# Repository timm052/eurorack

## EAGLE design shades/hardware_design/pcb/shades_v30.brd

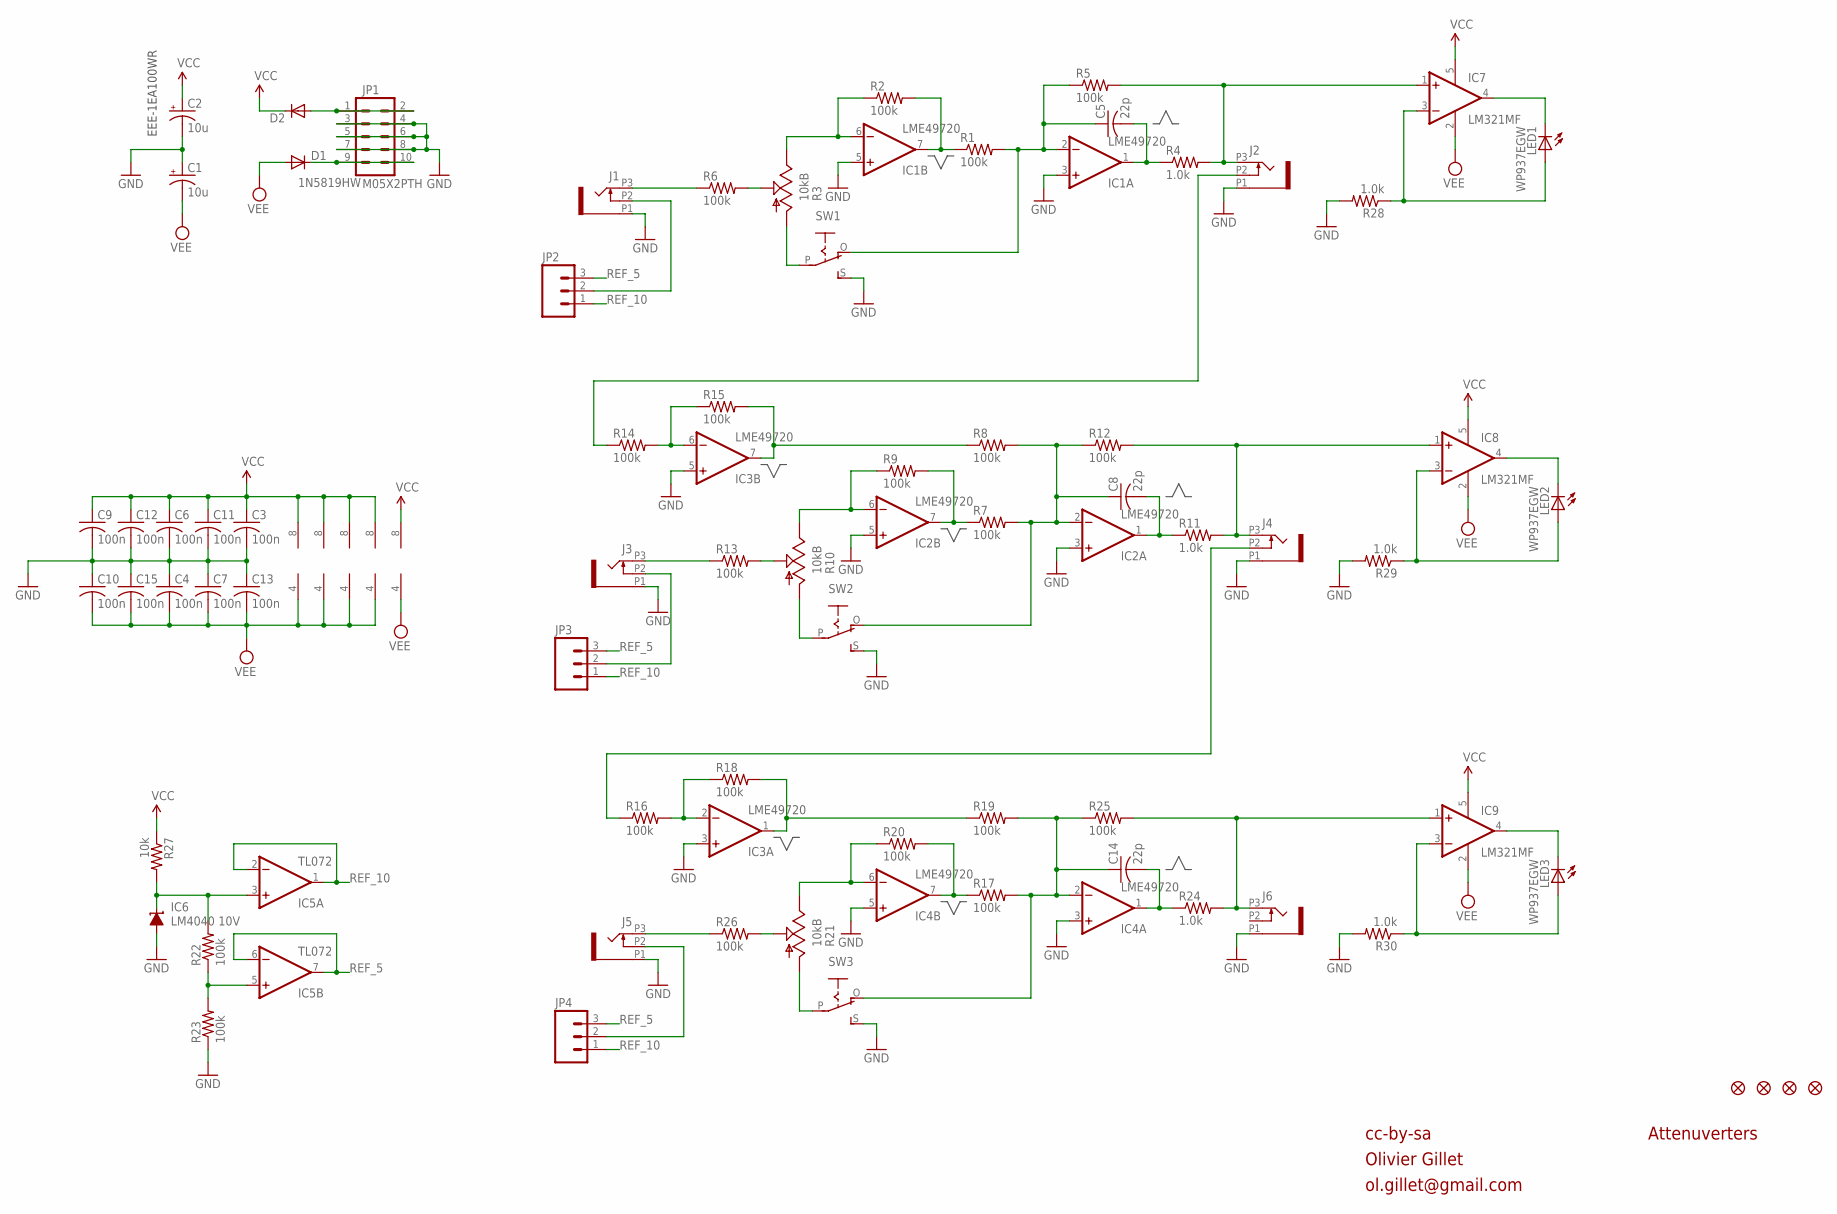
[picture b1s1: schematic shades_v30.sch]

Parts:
C1, C2: 10u; PANASONIC_B
C3, C4, C6, C7, C9, C10, C11, C12, C13, C15: 100n; C0603
C5, C8, C14: 22p; C0603
D1, D2: 1N5819HW; SOD123
F1, F2, F3, F4: FIDUCIAL1X2; FIDUCIAL-1X2
IC1, IC2, IC3, IC4: LME49720; SO08
IC5: TL072; SO08
IC6: LM4040 10V; DBZ_R-PDSO-G3
IC7, IC8, IC9: LM321MF; SOT23-5
J1, J2, J3, J4, J5, J6: PJ301_THONKICONN6; WQP_PJ_301M6
JP1: M05X2PTH; AVR_ICSP
JP2, JP3, JP4: M03PTH; 1X03
LED1, LED2, LED3: WP937EGW; LED3MM
R1, R2, R5, R6, R7, R8, R9, R12, R13, R14, R15, R16, R17, R18, R19, R20, R22, R23, R25, R26: 100k; R0603
R3, R10, R21: 10kB; ALPS_POT_VERTICAL_PS
R4, R11, R24, R28, R29, R30: 1.0k; R0603
R27: 10k; R0603
SW1, SW2, SW3: S-ON-ONSMALL_SLIDE; ES_100SP1T6B11M2QEH_SMALL

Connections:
GND: C1.+, C2.-, C3.2, C4.1, C6.2, C7.1, C9.2, C10.1, C11.2, C12.2, C13.1, C15.1, IC1.3 (+IN), IC1.5 (+IN), IC2.3 (+IN), IC2.5 (+IN), IC3.3 (+IN), IC3.5 (+IN), IC4.3 (+IN), IC4.5 (+IN), IC6.2 (A), J1.P1 (1), J2.P1 (1), J3.P1 (1), J4.P1 (1), J5.P1 (1), J6.P1 (1), JP1.3, JP1.4, JP1.5, JP1.6, JP1.7, JP1.8, R23.1, R28.2, R29.2, R30.2, SW1.S, SW2.S, SW3.S
unnamed: J1.P2 (2), JP2.2
unnamed: J3.P2 (2), JP3.2
unnamed: J5.P2 (2), JP4.2
unnamed: IC7.3 (-IN), LED1.A, R28.1
unnamed: IC5.5 (+IN), R22.1, R23.2
unnamed: D2.A, JP1.1, JP1.2
unnamed: IC7.4 (OUT), LED1.K (C)
unnamed: J1.P3 (3), R6.1
unnamed: R3.P$2 (S), R6.2
unnamed: R3.P$3 (A), SW1.P
unnamed: C5.1, IC1.2 (-IN), R1.2, R5.1, SW1.O
unnamed: IC1.6 (-IN), R2.1, R3.P$1 (E)
unnamed: IC1.7 (OUT), R1.1, R2.2
unnamed: C5.2, IC1.1 (OUT), R4.1
unnamed: J3.P3 (3), R13.1
unnamed: IC8.3 (-IN), LED2.A, R29.1
unnamed: R10.P$2 (S), R13.2
unnamed: R10.P$3 (A), SW2.P
unnamed: D1.C, JP1.9, JP1.10
unnamed: IC2.6 (-IN), R9.1, R10.P$1 (E)
unnamed: IC2.7 (OUT), R7.1, R9.2
unnamed: IC8.4 (OUT), LED2.K (C)
unnamed: C8.2, IC2.1 (OUT), R11.1
unnamed: J5.P3 (3), R26.1
unnamed: R21.P$2 (S), R26.2
unnamed: IC4.6 (-IN), R20.1, R21.P$1 (E)
unnamed: IC4.7 (OUT), R17.1, R20.2
unnamed: C14.2, IC4.1 (OUT), R24.1
unnamed: IC9.3 (-IN), LED3.A, R30.1
unnamed: IC9.4 (OUT), LED3.K (C)
unnamed: IC3.6 (-IN), R14.2, R15.1
unnamed: IC3.2 (-IN), R16.2, R18.1
unnamed: IC3.1 (OUT), R18.2, R19.1
unnamed: IC3.7 (OUT), R8.1, R15.2
unnamed: C14.1, IC4.2 (-IN), R17.2, R19.2, R25.1, SW3.O
unnamed: C8.1, IC2.2 (-IN), R7.2, R8.2, R12.1, SW2.O
OUT_1: IC7.1 (+IN), J2.P3 (3), R4.2, R5.2
OUT_2: IC8.1 (+IN), J4.P3 (3), R11.2, R12.2
OUT_3: IC9.1 (+IN), J6.P3 (3), R24.2, R25.2
REF_5: IC5.6 (-IN), IC5.7 (OUT), JP2.3, JP3.3, JP4.3
REF_10: IC5.1 (OUT), IC5.2 (-IN), JP2.1, JP3.1, JP4.1
REF_10_UNBUF: IC5.3 (+IN), IC6.1 (C), R22.2, R27.2
SEND_1: J2.P2 (2), R14.1
SEND_2: J4.P2 (2), R16.1
SW3: R21.P$3 (A), SW3.P
VCC: C2.+, C3.1, C6.1, C9.1, C11.1, C12.1, D2.C, IC1.8 (V+), IC2.8 (V+), IC3.8 (V+), IC4.8 (V+), IC5.8 (V+), IC7.5 (V+), IC8.5 (V+), IC9.5 (V+), R27.1
VEE: C1.-, C4.2, C7.2, C10.2, C13.2, C15.2, D1.A, IC1.4 (V-), IC2.4 (V-), IC3.4 (V-), IC4.4 (V-), IC5.4 (V-), IC7.2 (V-), IC8.2 (V-), IC9.2 (V-)

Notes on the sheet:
cc-by-sa
Olivier Gillet
ol.gillet@gmail.com
Attenuverters
EEE-1EA100WR

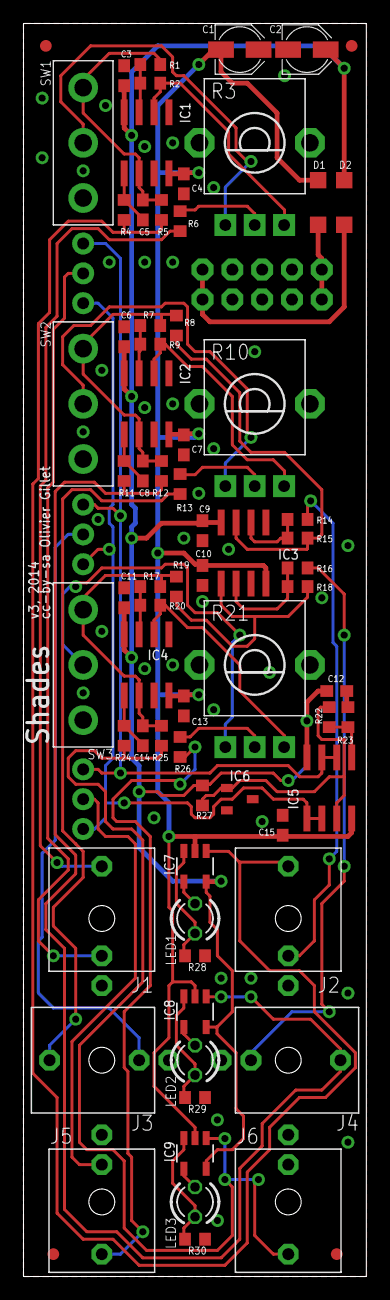
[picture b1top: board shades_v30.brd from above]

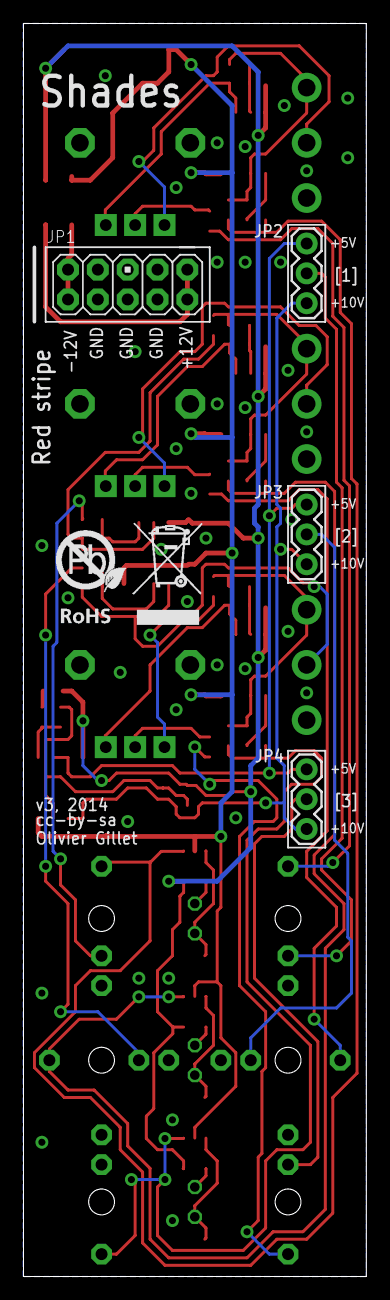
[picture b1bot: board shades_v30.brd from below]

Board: 2 copper layers, 29.2 x 106.7 mm, 77 parts (5 on the bottom side), 48 nets.

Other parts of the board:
U$2: ROHS

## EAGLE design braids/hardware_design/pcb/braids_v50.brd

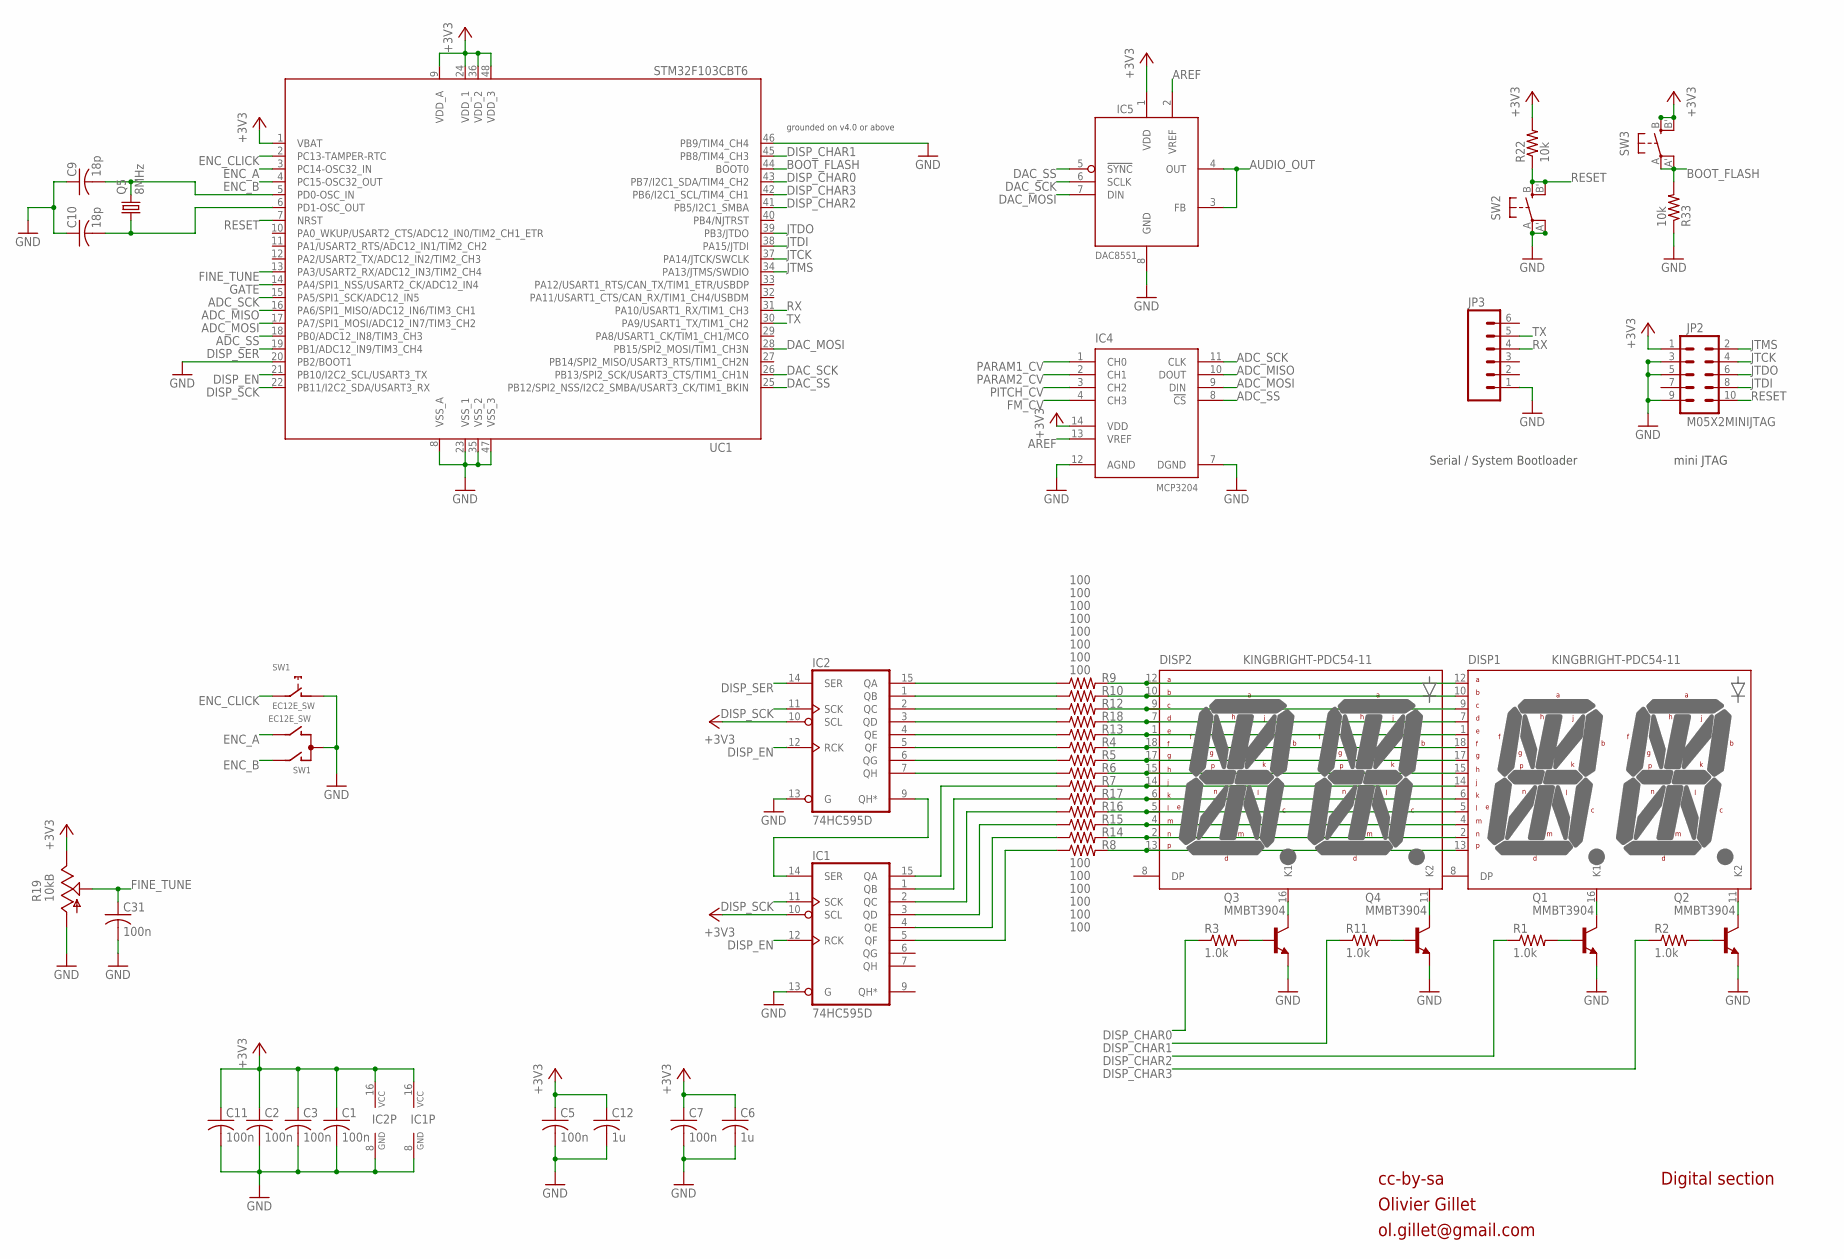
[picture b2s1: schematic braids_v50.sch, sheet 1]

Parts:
C1, C2, C3, C5, C7, C11, C31: 100n; C0603
C6, C12: 1u; C0603
C9, C10: 18p; C0603
DISP1, DISP2: KINGBRIGHT-PDC54-11; PDC54
IC1, IC2: 74HC595D; SO16
IC4: MCP3204; SO14
IC5: DAC8551; MSOP-8
JP2: M05X2MINIJTAG; 2X5-1.27
JP3: M06SIP; 1X06
Q1, Q2, Q3, Q4: MMBT3904; SOT23-BEC
Q5: 8MHz; HC49UP
R1, R2, R3, R11: 1.0k; R0603
R4, R5, R6, R7, R8, R9, R10, R12, R13, R14, R15, R16, R17, R18: 100; R0603
R19: 10kB; ALPS_POT_VERTICAL_PS
R22, R33: 10k; R0603
SW1: EC12E_SW; ALPS_EC12E_SW
SW2, SW3: EVQQ2; EVQ-Q2
UC1: STM32F103CBT6; LQFP48

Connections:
+3V3: C1.1, C2.1, C3.1, C5.1, C6.1, C7.1, C11.1, C12.1, IC1.10 (SCL), IC1.16 (VCC), IC2.10 (SCL), IC2.16 (VCC), IC4.14 (VDD), IC5.1 (VDD), JP2.1, R19.P$1 (E), R22.2, SW3.B (S), SW3.B' (S1), UC1.1 (VBAT), UC1.9 (VDD_A), UC1.24 (VDD_1), UC1.36 (VDD_2), UC1.48 (VDD_3); also elsewhere on the board
ADC_MISO: IC4.10 (DOUT), UC1.16 (PA6/SPI1_MISO/ADC12_IN6/TIM3_CH1)
ADC_MOSI: IC4.9 (DIN), UC1.17 (PA7/SPI1_MOSI/ADC12_IN7/TIM3_CH2)
ADC_SCK: IC4.11 (CLK), UC1.15 (PA5/SPI1_SCK/ADC12_IN5)
ADC_SS: IC4.8 (!CS), UC1.18 (PB0/ADC12_IN8/TIM3_CH3)
AREF: IC4.13 (VREF), IC5.2 (VREF); also elsewhere on the board
AUDIO_OUT: IC5.3 (FB), IC5.4 (OUT); also elsewhere on the board
BOOT_FLASH: R33.2, SW3.A, SW3.A' (P1), UC1.44 (BOOT0)
DAC_MOSI: IC5.7 (DIN), UC1.28 (PB15/SPI2_MOSI/TIM1_CH3N)
DAC_SCK: IC5.6 (SCLK), UC1.26 (PB13/SPI2_SCK/USART3_CTS/TIM1_CH1N)
DAC_SS: IC5.5 (!SYNC), UC1.25 (PB12/SPI2_NSS/I2C2_SMBA/USART3_CK/TIM1_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)
DISP_CHAR0: R3.1, UC1.43 (PB7/I2C1_SDA/TIM4_CH2)
DISP_CHAR1: R11.1, UC1.45 (PB8/TIM4_CH3)
DISP_CHAR2: R1.1, UC1.41 (PB5/I2C1_SMBA)
DISP_CHAR3: R2.1, UC1.42 (PB6/I2C1_SCL/TIM4_CH1)
DISP_EN: IC1.12 (RCK), IC2.12 (RCK), UC1.21 (PB10/I2C2_SCL/USART3_TX)
DISP_SCK: IC1.11 (SCK), IC2.11 (SCK), UC1.22 (PB11/I2C2_SDA/USART3_RX)
DISP_SER: IC2.14 (SER), UC1.19 (PB1/ADC12_IN9/TIM3_CH4)
ENC_A: SW1.B, UC1.3 (PC14-OSC32_IN)
ENC_B: SW1.A, UC1.4 (PC15-OSC32_OUT)
ENC_CLICK: SW1.E (2), UC1.2 (PC13-TAMPER-RTC)
FINE_TUNE: C31.1, R19.P$2 (S), UC1.13 (PA3/USART2_RX/ADC12_IN3/TIM2_CH4)
FM_CV: IC4.4 (CH3); also elsewhere on the board
GATE: UC1.14 (PA4/SPI1_NSS/USART2_CK/ADC12_IN4); also elsewhere on the board
GND: C1.2, C2.2, C3.2, C5.2, C6.2, C7.2, C9.1, C10.1, C11.2, C12.2, C31.2, IC1.8 (GND), IC1.13 (G), IC2.8 (GND), IC2.13 (G), IC4.7 (DGND), IC4.12 (AGND), IC5.8 (GND), JP2.3, JP2.5, JP2.9, JP3.1, Q1.E, Q2.E, Q3.E, Q4.E, R19.P$3 (A), R33.1, SW1.C, SW1.D (1), SW2.A, SW2.A' (P1), UC1.8 (VSS_A), UC1.20 (PB2/BOOT1), UC1.23 (VSS_1), UC1.35 (VSS_2), UC1.46 (PB9/TIM4_CH4), UC1.47 (VSS_3); also elsewhere on the board
JTCK: JP2.4, UC1.37 (PA14/JTCK/SWCLK)
JTDI: JP2.8, UC1.38 (PA15/JTDI)
JTDO: JP2.6, UC1.39 (PB3/JTDO)
JTMS: JP2.2, UC1.34 (PA13/JTMS/SWDIO)
unnamed: DISP2.16 (K1), Q3.C
unnamed: DISP2.11 (K2), Q4.C
unnamed: DISP1.16 (K1), Q1.C
unnamed: DISP1.11 (K2), Q2.C
unnamed: Q3.B, R3.2
unnamed: Q4.B, R11.2
unnamed: C9.2, Q5.2, UC1.5 (PD0-OSC_IN)
unnamed: C10.2, Q5.1, UC1.6 (PD1-OSC_OUT)
unnamed: Q1.B, R1.2
unnamed: Q2.B, R2.2
unnamed: DISP1.12 (A), DISP2.12 (A), R9.2
unnamed: DISP1.10 (B), DISP2.10 (B), R10.2
unnamed: DISP1.9 (C), DISP2.9 (C), R12.2
unnamed: DISP1.7 (D), DISP2.7 (D), R18.2
unnamed: DISP1.1 (E), DISP2.1 (E), R13.2
unnamed: DISP1.18 (F), DISP2.18 (F), R4.2
unnamed: DISP1.17 (G), DISP2.17 (G), R5.2
unnamed: DISP1.15 (H), DISP2.15 (H), R6.2
unnamed: DISP1.14 (J), DISP2.14 (J), R7.2
unnamed: DISP1.6 (K), DISP2.6 (K), R17.2
unnamed: DISP1.5 (L), DISP2.5 (L), R16.2
unnamed: DISP1.4 (M), DISP2.4 (M), R15.2
unnamed: DISP1.2 (N), DISP2.2 (N), R14.2
unnamed: DISP1.13, DISP2.13, R8.2
unnamed: IC2.7 (QH), R6.1
unnamed: IC1.14 (SER), IC2.9 (QH*)
unnamed: IC2.15 (QA), R9.1
unnamed: IC2.1 (QB), R10.1
unnamed: IC2.2 (QC), R12.1
unnamed: IC2.3 (QD), R18.1
unnamed: IC2.4 (QE), R13.1
unnamed: IC2.5 (QF), R4.1
unnamed: IC2.6 (QG), R5.1
unnamed: IC1.15 (QA), R7.1
unnamed: IC1.1 (QB), R17.1
unnamed: IC1.2 (QC), R16.1
unnamed: IC1.3 (QD), R15.1
unnamed: IC1.4 (QE), R14.1
unnamed: IC1.5 (QF), R8.1
PARAM1_CV: IC4.1 (CH0); also elsewhere on the board
PARAM2_CV: IC4.2 (CH1); also elsewhere on the board
PITCH_CV: IC4.3 (CH2); also elsewhere on the board
RESET: JP2.10, R22.1, SW2.B (S), SW2.B' (S1), UC1.7 (NRST)
RX: JP3.4, UC1.31 (PA10/USART1_RX/TIM1_CH3)
TX: JP3.5, UC1.30 (PA9/USART1_TX/TIM1_CH2)

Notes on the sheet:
cc-by-sa
Olivier Gillet
ol.gillet@gmail.com
Serial / System Bootloader
mini JTAG
Digital section
grounded on v4.0 or above

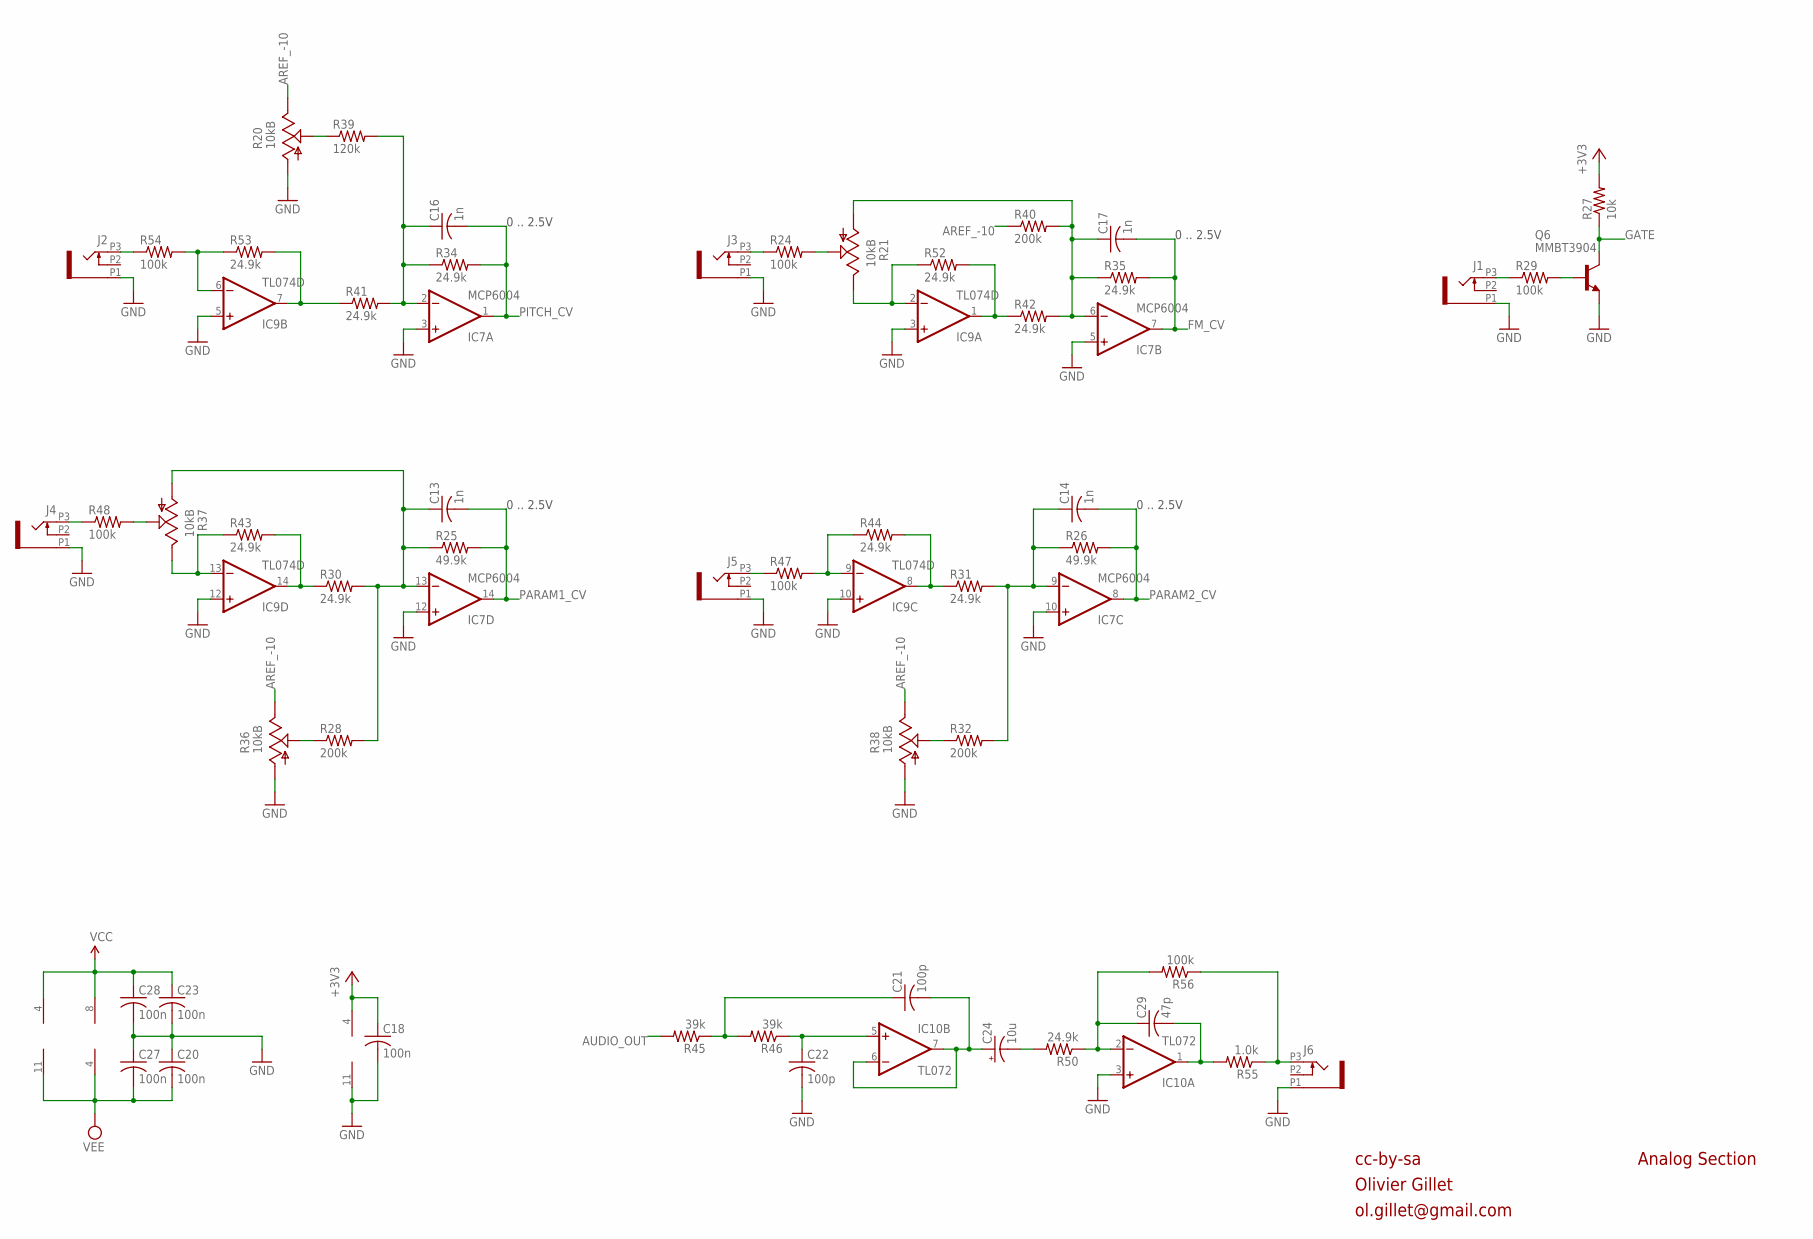
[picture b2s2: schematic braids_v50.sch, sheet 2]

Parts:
C13, C14, C16, C17: 1n; C0603
C18, C20, C23, C27, C28: 100n; C0603
C21, C22: 100p; C0603
C24: 10u; PANASONIC_B
C29: 47p; C0603
IC7: MCP6004; SO14
IC9: TL074D; SO14
IC10: TL072; SO08
J1, J2, J3, J4, J5, J6: PJ301_THONKICONN6; WQP_PJ_301M6
Q6: MMBT3904; SOT23-BEC
R20, R21, R36, R37, R38: 10kB; ALPS_POT_VERTICAL_PS
R24, R29, R47, R48, R54, R56: 100k; R0603
R25, R26: 49.9k; R0603
R27: 10k; R0603
R28, R32, R40: 200k; R0603
R30, R31, R34, R35, R41, R42, R43, R44, R50, R52, R53: 24.9k; R0603
R39: 120k; R0603
R45, R46: 39k; R0603
R55: 1.0k; R0603

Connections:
+3V3: C18.1, IC7.4 (V+), R27.2; also elsewhere on the board
AREF_-10: R20.P$1 (E), R36.P$1 (E), R38.P$1 (E), R40.1; also elsewhere on the board
AUDIO_OUT: R45.2; also elsewhere on the board
FM_CV: C17.2, IC7.7 (OUT), R35.2; also elsewhere on the board
GATE: Q6.C, R27.1; also elsewhere on the board
GND: C18.2, C20.1, C22.2, C23.2, C27.1, C28.2, IC7.3 (+IN), IC7.5 (+IN), IC7.10 (+IN), IC7.11 (V-), IC7.12 (+IN), IC9.3 (+IN), IC9.5 (+IN), IC9.10 (+IN), IC9.12 (+IN), IC10.3 (+IN), J1.P1 (1), J2.P1 (1), J3.P1 (1), J4.P1 (1), J5.P1 (1), J6.P1 (1), Q6.E, R20.P$3 (A), R36.P$3 (A), R38.P$3 (A); also elsewhere on the board
unnamed: IC9.7 (OUT), R41.1, R53.2
unnamed: R20.P$2 (S), R39.1
unnamed: J2.P3 (3), R54.1
unnamed: C16.1, IC7.2 (-IN), R34.1, R39.2, R41.2
unnamed: IC9.6 (-IN), R53.1, R54.2
unnamed: J3.P3 (3), R24.1
unnamed: J4.P3 (3), R48.1
unnamed: R21.P$2 (S), R24.2
unnamed: IC9.13 (-IN), R37.P$1 (E), R43.1
unnamed: IC9.14 (OUT), R30.1, R43.2
unnamed: IC9.2 (-IN), R21.P$1 (E), R52.1
unnamed: IC9.1 (OUT), R42.1, R52.2
unnamed: C17.1, IC7.6 (-IN), R21.P$3 (A), R35.1, R40.2, R42.2
unnamed: J1.P3 (3), R29.1
unnamed: IC9.8 (OUT), R31.1, R44.2
unnamed: C13.1, IC7.13 (-IN), R25.1, R28.2, R30.2, R37.P$3 (A)
unnamed: J5.P3 (3), R47.1
unnamed: R28.1, R36.P$2 (S)
unnamed: R37.P$2 (S), R48.2
unnamed: IC9.9 (-IN), R44.1, R47.2
unnamed: R32.1, R38.P$2 (S)
unnamed: Q6.B, R29.2
unnamed: C21.2, C24.+, IC10.6 (-IN), IC10.7 (OUT)
unnamed: C24.-, R50.2
unnamed: C22.1, IC10.5 (+IN), R46.1
unnamed: C14.1, IC7.9 (-IN), R26.1, R31.2, R32.2
unnamed: C21.1, R45.1, R46.2
unnamed: J6.P3 (3), R55.1, R56.1
unnamed: C29.2, IC10.1 (OUT), R55.2
unnamed: C29.1, IC10.2 (-IN), R50.1, R56.2
PARAM1_CV: C13.2, IC7.14 (OUT), R25.2; also elsewhere on the board
PARAM2_CV: C14.2, IC7.8 (OUT), R26.2; also elsewhere on the board
PITCH_CV: C16.2, IC7.1 (OUT), R34.2; also elsewhere on the board
VCC: C23.1, C28.1, IC9.4 (V+), IC10.8 (V+); also elsewhere on the board
VEE: C20.2, C27.2, IC9.11 (V-), IC10.4 (V-); also elsewhere on the board

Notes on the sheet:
cc-by-sa
Olivier Gillet
ol.gillet@gmail.com
Analog Section
0 .. 2.5V

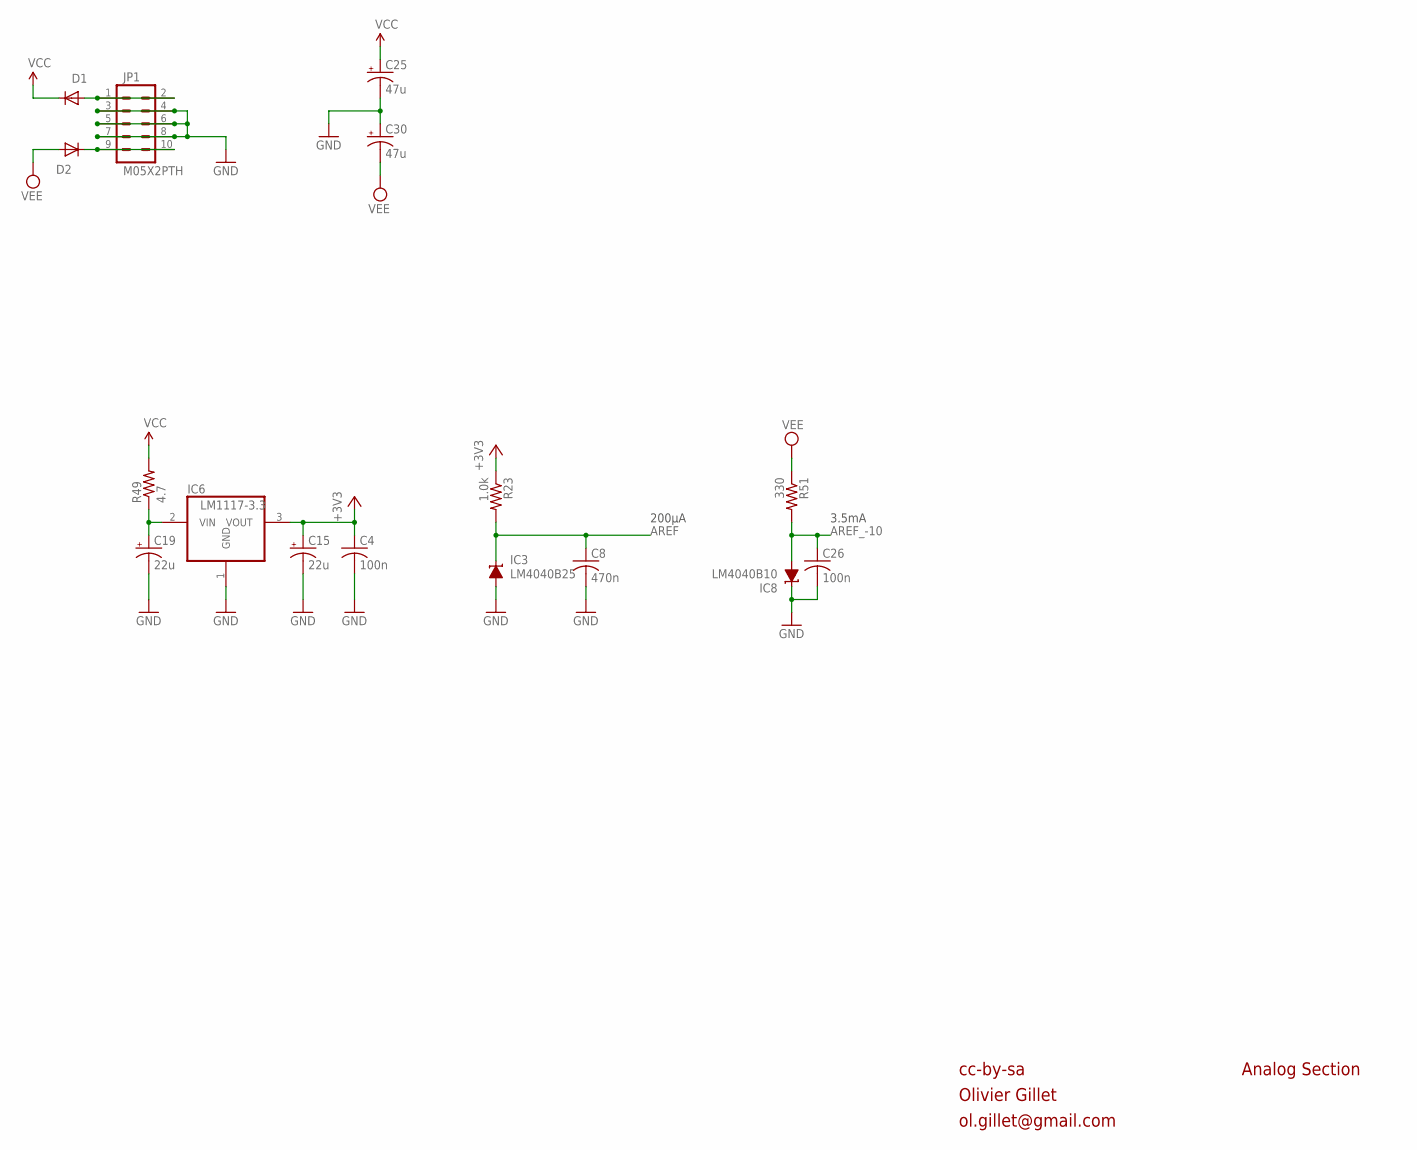
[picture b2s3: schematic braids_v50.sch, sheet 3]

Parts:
C4, C26: 100n; C0603
C8: 470n; C0603
C15, C19: 22u; PANASONIC_C
C25, C30: 47u; PANASONIC_D
D1, D2: 1N5819HW; SOD123
IC3: LM4040B25; DBZ_R-PDSO-G3
IC6: LM1117-3.3; TO252
IC8: LM4040B10; DBZ_R-PDSO-G3
JP1: M05X2PTH; AVR_ICSP
R23: 1.0k; R0603
R49: 4.7; R1206
R51: 330; R0603

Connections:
+3V3: C4.1, C15.+, IC6.3 (VOUT), R23.1; also elsewhere on the board
AREF: C8.1, IC3.1 (C), R23.2; also elsewhere on the board
AREF_-10: C26.1, IC8.2 (A), R51.2; also elsewhere on the board
GND: C4.2, C8.2, C15.-, C19.-, C25.-, C26.2, C30.+, IC3.2 (A), IC6.1 (GND), IC8.1 (C), JP1.3, JP1.4, JP1.5, JP1.6, JP1.7, JP1.8; also elsewhere on the board
unnamed: C19.+, IC6.2 (VIN), R49.1
unnamed: D1.A, JP1.1, JP1.2
unnamed: D2.C, JP1.9, JP1.10
VCC: C25.+, D1.C, R49.2; also elsewhere on the board
VEE: C30.-, D2.A, R51.1; also elsewhere on the board

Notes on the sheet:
3.5mA
200µA
cc-by-sa
Olivier Gillet
ol.gillet@gmail.com
Analog Section

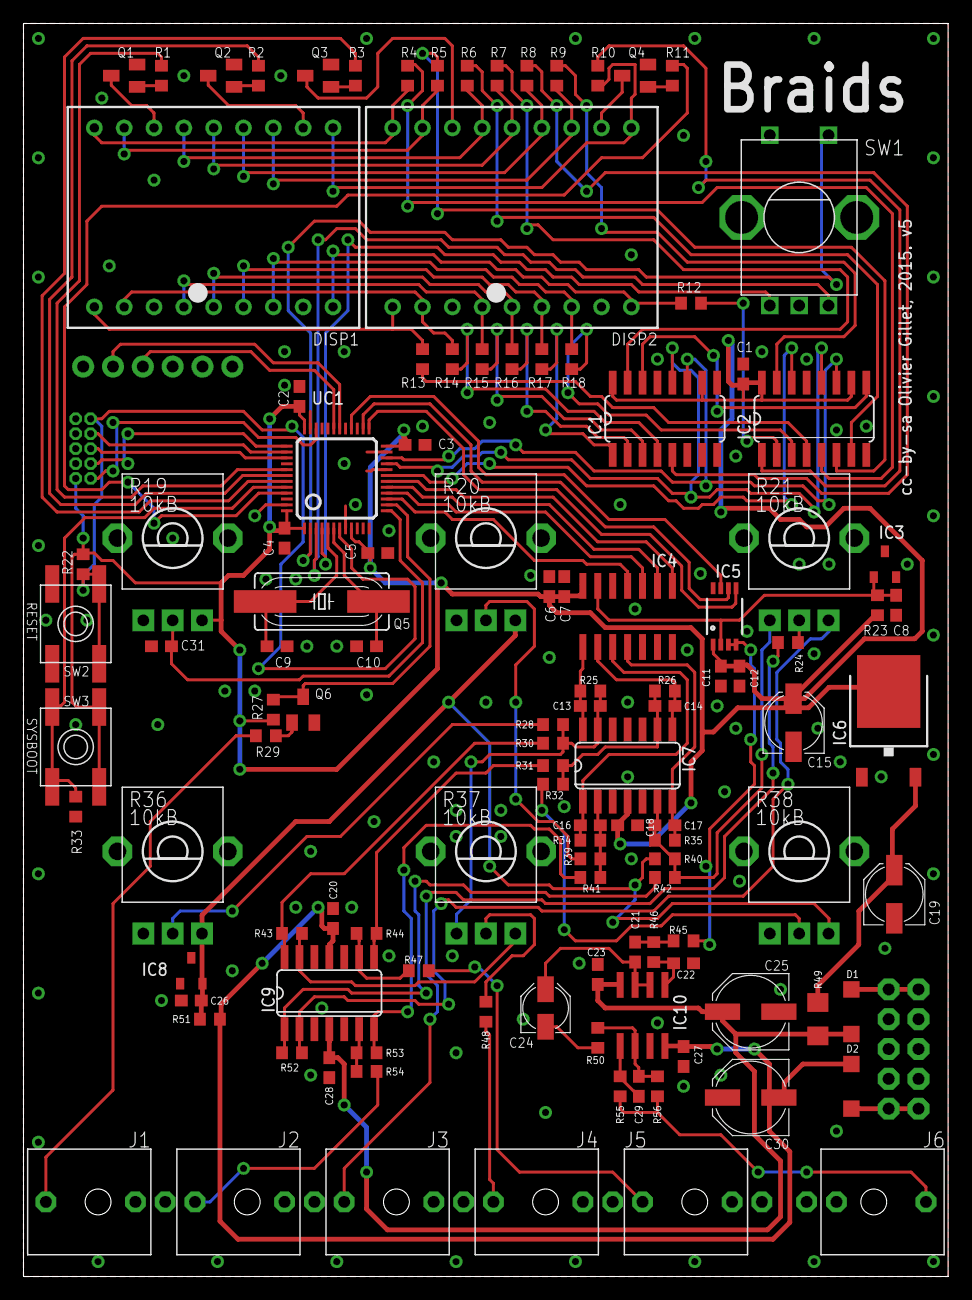
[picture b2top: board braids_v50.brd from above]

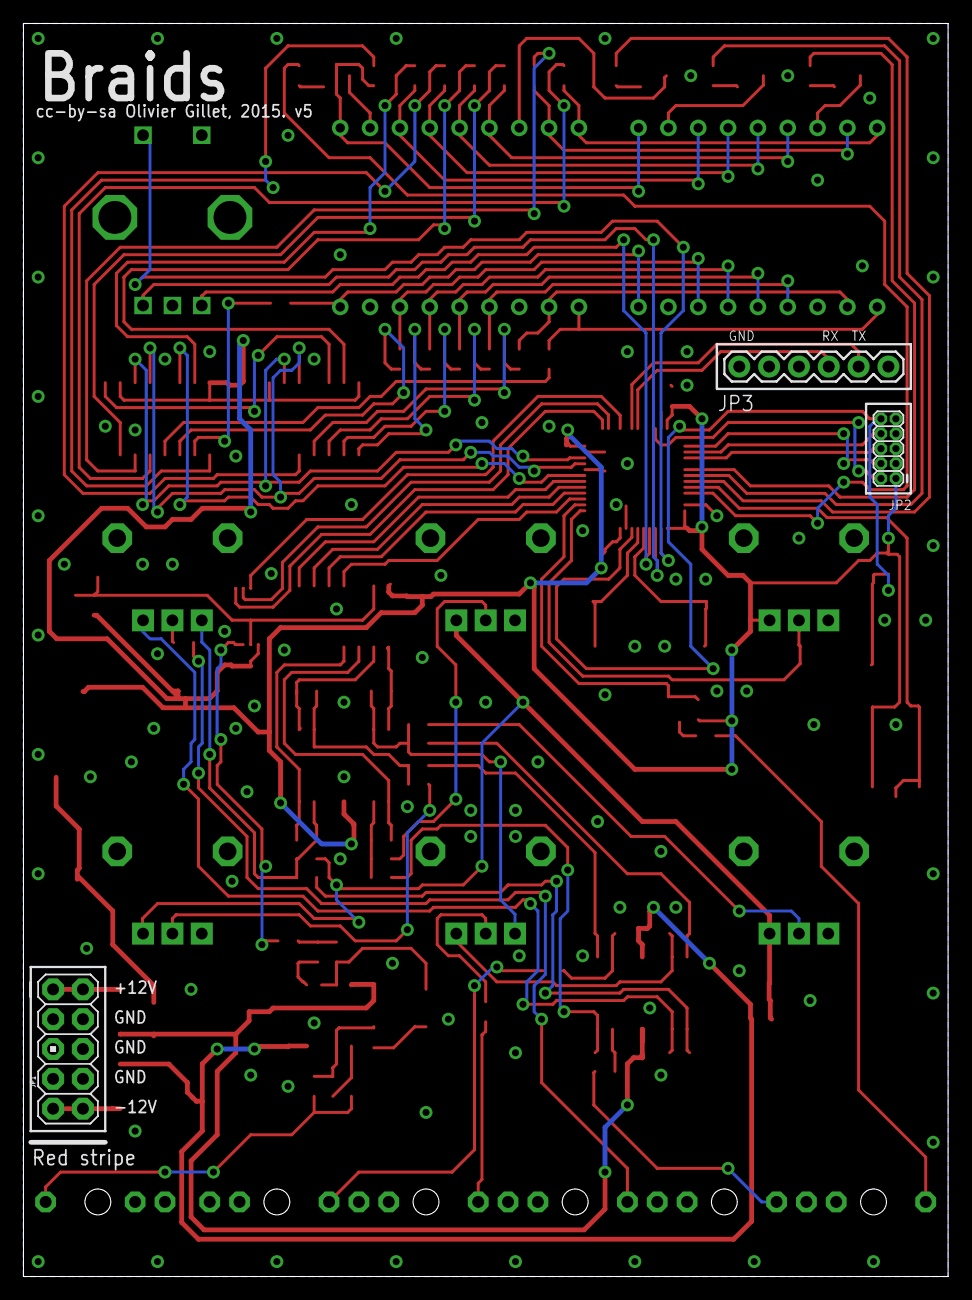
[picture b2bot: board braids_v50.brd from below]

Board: 2 copper layers, 78.7 x 106.7 mm, 120 parts (3 on the bottom side), 110 nets.
